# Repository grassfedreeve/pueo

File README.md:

# pueo
26-key, column-staggered, wireless, reversable, split keyboard made with [ergogen](https://github.com/ergogen/ergogen) and [KiCad](https://www.kicad.org/). Named after the [pueo](https://en.wikipedia.org/wiki/Pueo).

Highly inspired by the [TOTEM](https://github.com/GEIGEIGEIST/TOTEM) by [GEIST](https://github.com/GEIGEIGEIST/), the [zilpzalp](https://github.com/kilipan/zilpzalp), [the berylline](https://github.com/jcmkk3/trochilidae#berylline), and my unibody board the [ʻākohekohe](https://github.com/grassfedreeve/akohekohe/).

Two versions for choc switches are available:
- The default-spacing solder-only version (in the [pcb](https://github.com/grassfedreeve/pueo/tree/main/pcb) directory)
- The minimal-choc-spacing solder-only version with the tightest spacing that choc V1 switches allow for (in the [pcb_min_choc](https://github.com/grassfedreeve/pueo/tree/main/pcb_min_choc) directory)
  **Note:** You will have to procure min-spacing keycaps. I am not aware of any commercial solution. Recommendation: [Philadelphia Minimalist](https://github.com/pseudoku/PseudoMakeMeKeyCapProfiles/blob/master/Philadelphia_Minimalist.scad) by [Pseudoku](https://github.com/pseudoku). There are also currently no 1.5u min-space keycaps, these will need to be generated.

**Warning:** The min-choc-spacing version has not been tested yet!

# Keymap
Example keymap for how you might use this many keys, created using caksoylar's great [keymap-drawer](https://github.com/caksoylar/keymap-drawer)

Alternative base layouts, Colemak DH, [Bird](https://github.com/jcmkk3/bird-layout), and a Gallium mod shared to me by [ssbb](https://github.com/ssbb) are also great options:

## BOM
- 2 pcbs
- 2 nice!nanos v2
- 26 kailh choc low profile switches
- 26 keycaps
- 2 100mAh 401230 batteries
- 2 6-pin vertical power switchs such as [these](https://www.amazon.com/dp/B01E3G12YY?)
- 2 [reset buttons TS-1236-4.3](https://www.aliexpress.com/item/1005001629184984.html)]

# Tenting
The pueo was built intending to be used with the great [SpitKB Tenting Puck](https://splitkb.com/products/tenting-puck) and mounted on smallrig magic arms. As of publishing the board they were out of stock so I am using magnetic rings for now.

## Firmware
ZMK is what I use and have setup a module for: [peuo ZMK Module](https://github.com/grassfedreeve/zmk-keyboards-pueo)

## Inspiration & Thanks
- GEIST's [TOTEM](https://github.com/GEIGEIGEIST/TOTEM) keyboard
- jcmkk3's [berylline](https://github.com/jcmkk3/trochilidae#berylline) and rufous which I based the ergogen config on and used their great footprints.
- apfel's [zilpzalp](https://github.com/kilipan/zilpzalp) keyboard
- PJE66's [hummingbird](https://github.com/PJE66/hummingbird) keyboard
- Weteor's [grumpy](https://github.com/weteor/Grumpy) and [fitis](https://github.com/weteor/fitis)
- apsu's [aptmak](https://github.com/apsu/aptmak) keyboard layout

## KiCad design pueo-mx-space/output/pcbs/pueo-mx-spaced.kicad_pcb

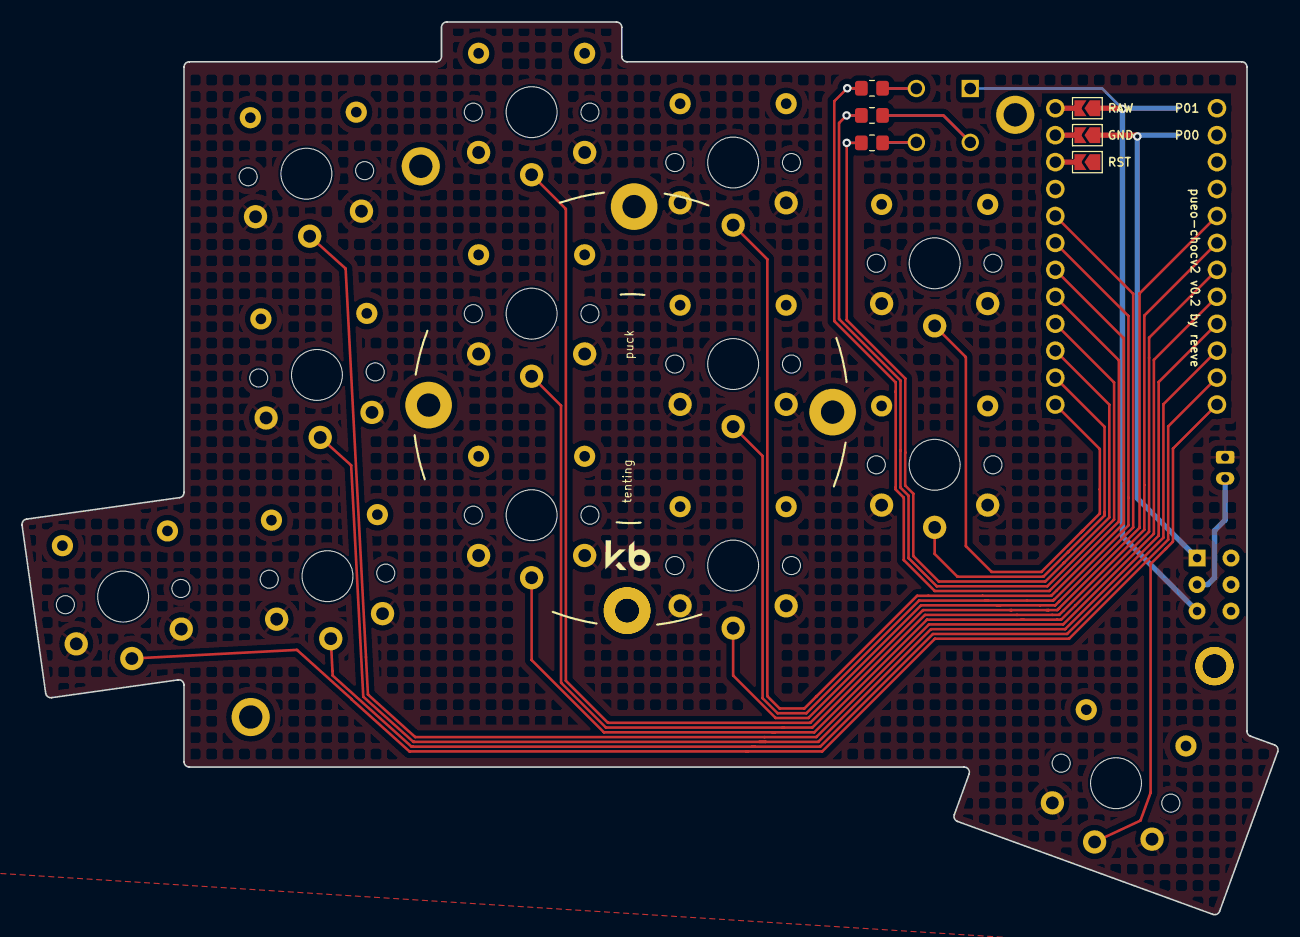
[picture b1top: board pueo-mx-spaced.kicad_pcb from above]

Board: 2 copper layers, 118.4 x 84.2 mm, 15 parts (1 on the bottom side), 15 nets.

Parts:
MCU1: ProMicroSimpleJumper
S1, S2, S3, S4, S5, S6, S7, S8, S9, S10, S11, S12, S13: ChocV2SimpleReversible
on/off: SW_E-Switch_EG1271_SPDT

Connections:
GND: MCU1.2, S1.2, S1.3, S2.2, S2.3, S3.2, S3.3, S4.2, S4.3, S5.2, S5.3, S6.2, S6.3, S7.2, S7.3, S8.2, S8.3, S9.2, S9.3, S10.2, S10.3, S11.2, S11.3, S12.2, S12.3, S13.2, S13.3, on/off.1
P2: MCU1.17, S8.1
P3: MCU1.18, S9.1
P4: MCU1.19, S10.1
P8: MCU1.23, S11.1
P9: MCU1.24, S12.1
P10: MCU1.12, S13.1
P14: MCU1.10, S2.1
P15: MCU1.9, S3.1
P16: MCU1.11, S1.1
P18: MCU1.8, S4.1
P19: MCU1.7, S5.1
P20: MCU1.6, S6.1
P21: MCU1.5, S7.1
RAW: MCU1.1, on/off.3

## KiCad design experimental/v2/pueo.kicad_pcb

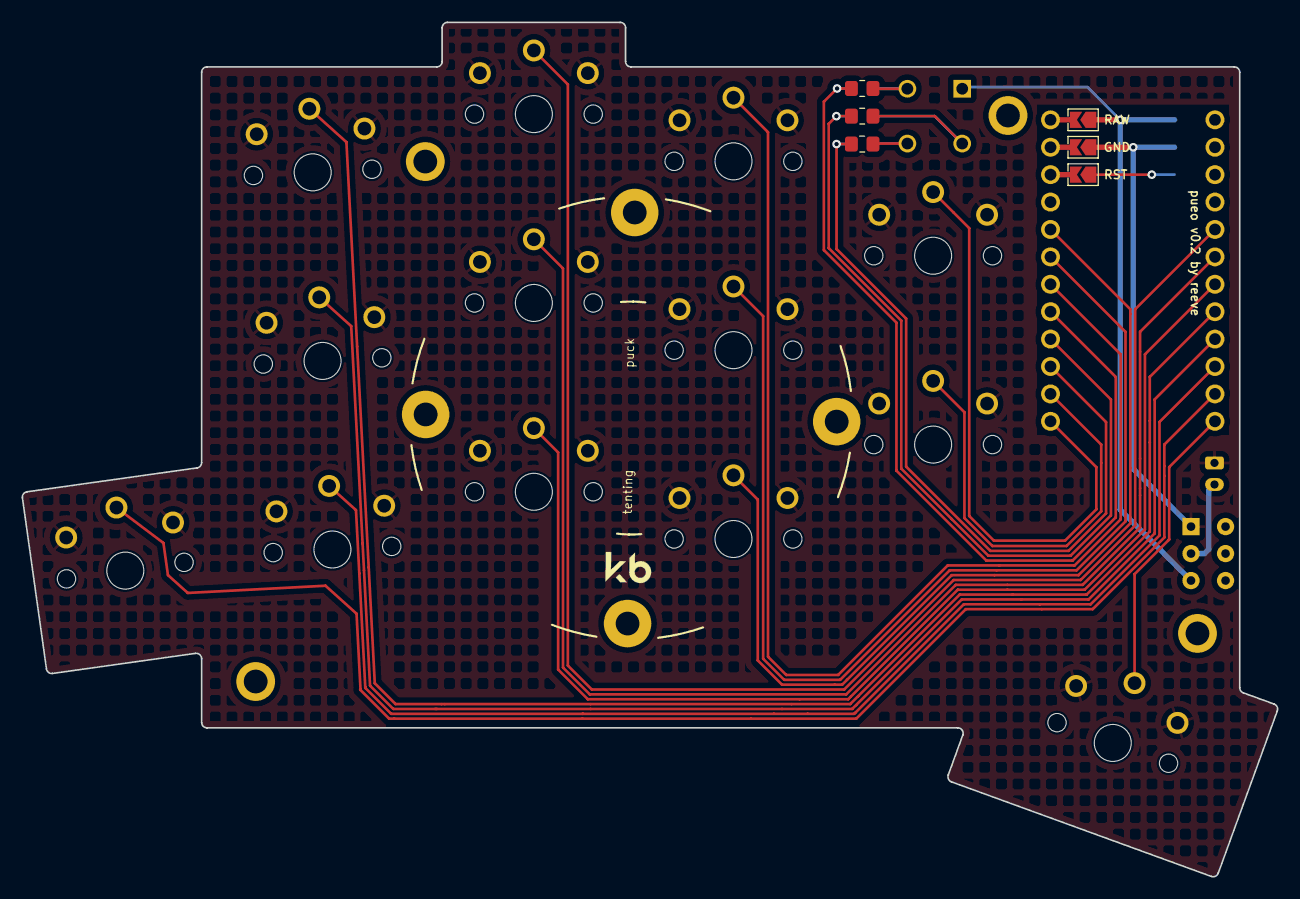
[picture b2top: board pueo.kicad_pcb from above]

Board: 2 copper layers, 116.3 x 79.2 mm, 15 parts (1 on the bottom side), 15 nets.

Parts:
MCU1: ProMicroSimpleJumper
S1, S2, S3, S4, S5, S6, S7, S8, S9, S10, S11, S12, S13: ChocSimpleReversible
on/off: SW_E-Switch_EG1271_SPDT

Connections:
GND: MCU1.2, S1.1, S2.1, S3.1, S4.1, S5.1, S6.1, S7.1, S8.1, S9.1, S10.1, S11.1, S12.1, S13.1, on/off.1
P2: MCU1.17, S8.2
P3: MCU1.18, S9.2
P4: MCU1.19, S10.2
P8: MCU1.23, S11.2
P9: MCU1.24, S12.2
P10: MCU1.12, S13.2
P14: MCU1.10, S2.2
P15: MCU1.9, S3.2
P16: MCU1.11, S1.2
P18: MCU1.8, S4.2
P19: MCU1.7, S5.2
P20: MCU1.6, S6.2
P21: MCU1.5, S7.2
RAW: MCU1.1, on/off.3

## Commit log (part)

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2024-10-10 crop photo and fix readme
2024-10-10 add firmware submodule
2024-10-10 license
2024-12-08 experimentalv2-v2mxspace-v2-24key
